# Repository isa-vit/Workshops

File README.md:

<br>
<h2 align=center>Find the resources here!</h2>
<br>

<table cellspacing="50" align=center>
  <tr>
    <td align=center>
      <h3>Technitude/Workshop</h3>
    </td>
    <td align=center>
      <h3>Resources</h3>
    </td>
    <td align=center>
      <h3>Video</h3>
    </td>
  </tr> 
   <tr>
    <td align=center>
      <h4>PCB Design</h4>
    </td>
    <td align=center>
      
    </td>
    <td align=center>
      
    </td>
  </tr>
  <tr>
    <td align=center>
      <h4>Data Analysis with Python using NumPy and Pandas</h4>
    </td>
    <td align=center>
      
    </td>
    <td align=center>
      
    </td>
  </tr>
  
  <tr>
    <td align=center>
      <h4>Introduction to Web Dev - ThreeJS and WebGL</h4>
    </td>
    <td align=center>
      
    </td>
    <td align=center>
      
    </td>
  </tr>

  <tr>
    <td align=center>
      <h4>Applications of AR in Interactive Technology</h4>
    </td>
    <td align=center>
    
    </td>
    <td align=center>
      
    </td>
  </tr>
  
  <tr>
    <td align=center>
      <h4>Applications of ML in Accident Fatality Prediction</h4>
    </td>
    <td align=center>
    
    </td>
    <td align=center>
      
    </td>
  </tr>
</table>

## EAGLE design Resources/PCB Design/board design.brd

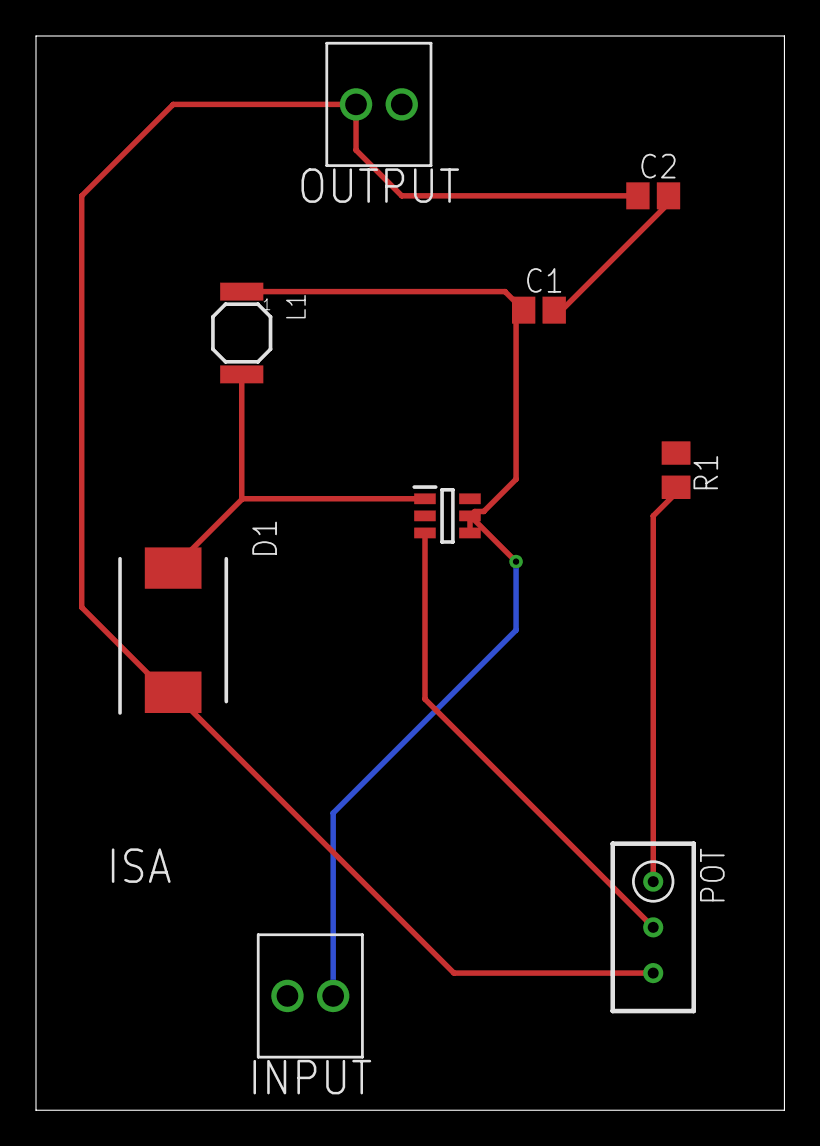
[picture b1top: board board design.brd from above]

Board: 2 copper layers, 41.6 x 59.7 mm, 9 parts (0 on the bottom side), 6 nets.

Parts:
C1, C2: C0805
D1: SS34; DIOM7959X262N
INPUT: 2828XX-2282834-2; TERMBLK_254-2N
L1: MS42
OUTPUT: 2828XX-2282834-2; TERMBLK_254-2N
POT: RTRIM3296W
R1: M0805
U1: MT3608; SOT95P280X145-6N

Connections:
GND: C1.2, C2.2, INPUT.1, OUTPUT.2, R1.1, U1.2
IND: D1.2, L1.1, U1.1
unnamed: C1.1, INPUT.2, L1.2, U1.4, U1.5
unnamed: POT.1, R1.2
unnamed: POT.2, U1.3
unnamed: C2.1, D1.1, OUTPUT.1, POT.3

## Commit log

2021-11-18 technitude-1
2021-11-18 technitude 1
2021-11-18 technitude 2
2021-11-20 technitude 3
2021-11-22 Technitude resources
2021-11-22 Readme updated
2021-11-23 Technitude 4
2021-11-28 Resources added
2021-11-28 Added the final notebook and committed the initial notebook
